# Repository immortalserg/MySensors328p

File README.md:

# MySensors328p

Проект по разработке оборудования на микросхеме Atmega328p+Nrf24l01+

## MySensorsKey

4-х клавишный сенсорный выключатель
- беспроводной приемник-передатчик nrf24l01+
- управляющий процессор Atmega 328p с возможностью шифрования (ATSHA204-TSU) и дополнительной памятью (AT25xx).
- 4 сенсорные кнопки на микросхеме TTP224
- встроенный датчик температуры, давления и влажности BME280
- встроенный USB-UART преобразователь на микросхеме CP2102
- контроллер заряда аккумулятора (TP4056)
- аккумулятор 3,7 В формафактора до 70мм-50мм (рекомендуемый 305570 (55мм-70мм-3мм))

Корпус https://www.tinkercad.com/things/eCkWAxR6Mgm-mysensorskey#/

## MysensorsSensor

Универсальный датчик
- беспроводной приемник-передатчик nrf24l01+
- управляющий процессор Atmega 328p с возможностью шифрования (ATSHA204-TSU) и дополнительной памятью (AT25xx).
- встроенный датчик температуры, давления и влажности BME280
- встроенный USB-UART преобразователь на микросхеме CP2102
- контроллер заряда аккумулятора (TP4056)
- счетчик DS2423
- дополнительные выводы Atmega 328p
- аккумулятор 3,7 В формафактора 402020(20мм-20мм-4мм), 502020(20мм-20мм-5мм), 602020(20мм-20мм-5мм)

## MySensorsShield

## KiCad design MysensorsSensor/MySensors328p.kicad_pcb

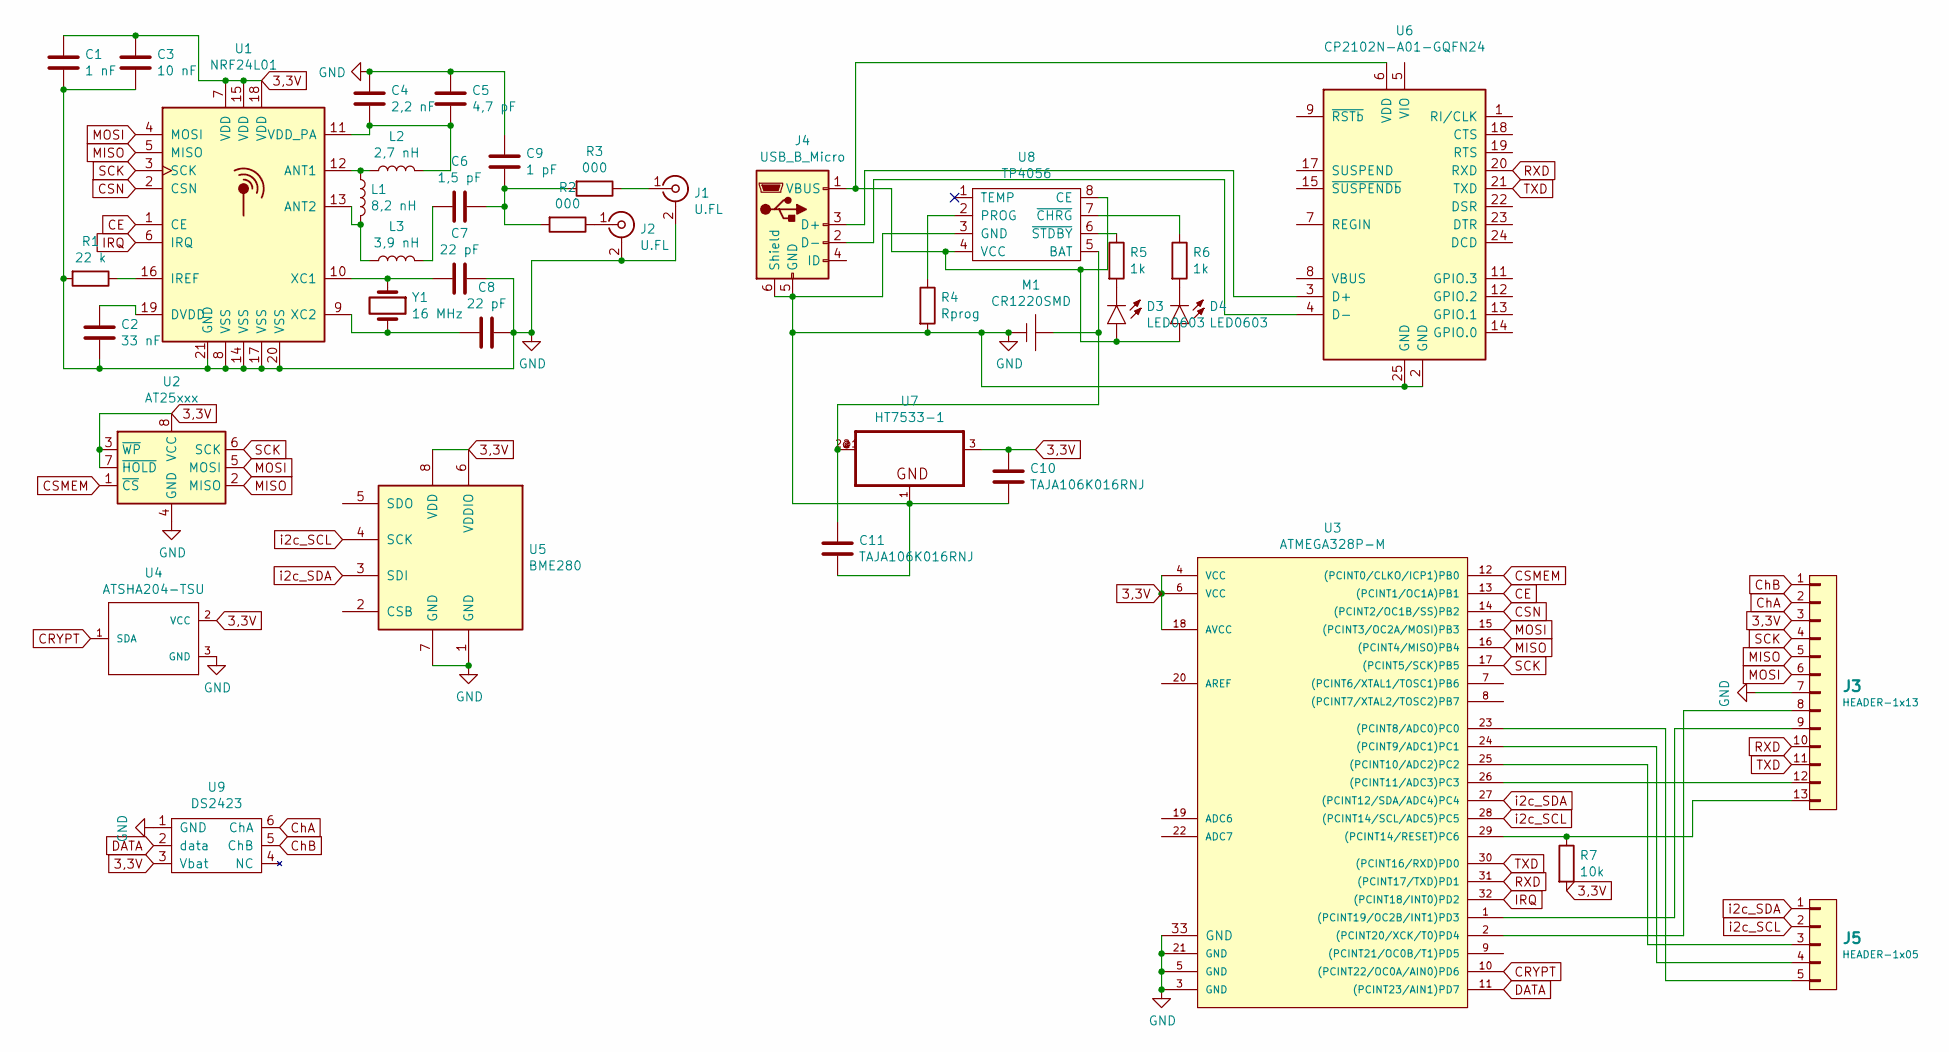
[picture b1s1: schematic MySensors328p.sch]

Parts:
C1: 1 nF; C_0402_1005Metric
C2: 33 nF; C_0402_1005Metric
C3: 10 nF; C_0402_1005Metric
C4: 2,2 nF; C_0402_1005Metric
C5: 4,7 pF; C_0402_1005Metric
C6: 1,5 pF; C_0402_1005Metric
C7, C8: 22 pF; C_0402_1005Metric
C9: 1 pF; C_0402_1005Metric
C10, C11: TAJA106K016RNJ; C_1206_3216Metric
D3, D4: LED0603; LED-0603
J1: U.FL; Texas_SWRA117D_2.4GHz_Right
J2: U.FL; U.FL_Hirose_U.FL-R-SMT-1_Vertical
J3: HEADER-1x13; PinHeader_1x13_P1.27mm_Vertical
J4: USB_B_Micro; USB_Micro-B_Molex_47346-0001
J5: HEADER-1x05; PinHeader_1x05_P1.27mm_Vertical
L1: 8,2 nH; L_0402_1005Metric
L2: 2,7 nH; L_0402_1005Metric
L3: 3,9 nH; L_0402_1005Metric
M1: CR1220SMD; WP-50mil-1x02
R1: 22 k; R_0402_1005Metric
R2, R3: 000; R_0402_1005Metric
R4: Rprog; R_0402_1005Metric
R5, R6: 1k; R_0402_1005Metric
R7: 10k; R_0402_1005Metric
U1: NRF24L01; QFN-20-1EP_4x4mm_P0.5mm_EP2.5x2.5mm
U2: AT25xxx; SOIC-8_3.9x4.9mm_P1.27mm
U3: ATMEGA328P-M; QFN-32-1EP_5x5mm_P0.5mm_EP3.45x3.45mm
U4: ATSHA204-TSU; SOT-23
U5: BME280; bme280
U6: CP2102N-A01-GQFN24; QFN-24-1EP_4x4mm_P0.5mm_EP2.6x2.6mm
U7: HT7533-1; SOT-89-3
U8: TP4056; PPSOP8
U9: DS2423; tsoc-6
Y1: 16 MHz; Crystal_SMD_5032-2Pin_5.0x3.2mm

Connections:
3,3V: C1.1, C3.1, C10.1, J3.3, R7.2, U1.7 (VDD), U1.15 (VDD), U1.18 (VDD), U2.3 (~WP), U2.7 (~HOLD), U2.8 (VCC), U3.4 (VCC), U3.6 (VCC), U3.18 (AVCC), U4.2 (VCC), U5.6 (VDDIO), U5.8 (VDD), U7.3 (VO), U9.3 (Vbat)
CE: U1.1 (CE), U3.13 ((PCINT1/OC1A)PB1)
CRYPT: U3.10 ((PCINT22/OC0A/AIN0)PD6), U4.1 (SDA)
CSMEM: U2.1 (~CS), U3.12 ((PCINT0/CLKO/ICP1)PB0)
CSN: U1.2 (CSN), U3.14 ((PCINT2/OC1B/SS)PB2)
ChA: J3.2, U9.6 (ChA)
ChB: J3.1, U9.5 (ChB)
DATA: U3.11 ((PCINT23/AIN1)PD7), U9.2 (data)
GND: C1.2, C2.2, C3.2, C4.1, C5.1, C7.1, C8.1, C9.1, C10.2, C11.2, J1.2 (Ext), J2.2 (Ext), J3.7, J4.5 (GND), J4.6 (Shield), M1.1 (-), R1.2, R4.2, U1.8 (VSS), U1.14 (VSS), U1.17 (VSS), U1.20 (VSS), U1.21 (GND), U2.4 (GND), U3.3 (GND), U3.5 (GND), U3.21 (GND), U3.33 (GND), U4.3 (GND), U5.1 (GND), U5.7 (GND), U6.2 (GND), U6.25 (GND), U7.1 (GND), U8.3 (GND), U9.1 (GND)
IRQ: U1.6 (IRQ), U3.32 ((PCINT18/INT0)PD2)
MISO: J3.5, U1.5 (MISO), U2.2 (MISO), U3.16 ((PCINT4/MISO)PB4)
MOSI: J3.6, U1.4 (MOSI), U2.5 (MOSI), U3.15 ((PCINT3/OC2A/MOSI)PB3)
unnamed: C2.1, U1.19 (DVDD)
unnamed: C4.2, C5.2, L2.2, U1.11 (VDD_PA)
unnamed: C6.1, C9.2, R2.2, R3.2
unnamed: C6.2, L3.2
unnamed: C7.2, U1.10 (XC1), Y1.1
unnamed: C8.2, U1.9 (XC2), Y1.2
unnamed: C11.1, M1.2 (+), U7.2 (VI), U7.2@1 (VI), U8.5 (BAT)
unnamed: D3.A, D4.A, J4.1 (VBUS), U6.6 (VDD), U8.4 (VCC), U8.8 (CE)
unnamed: D3.C, R5.2
unnamed: D4.C, R6.2
unnamed: J1.1 (In), R3.1
unnamed: J2.1 (In), R2.1
unnamed: J3.8, U3.2 ((PCINT20/XCK/T0)PD4)
unnamed: J3.9, U3.1 ((PCINT19/OC2B/INT1)PD3)
unnamed: J3.12, U3.26 ((PCINT11/ADC3)PC3)
unnamed: J3.13, R7.1, U3.29 ((PCINT14/RESET)PC6)
unnamed: J4.2 (D-), U6.4 (D-)
unnamed: J4.3 (D+), U6.3 (D+)
unnamed: J5.3, U3.25 ((PCINT10/ADC2)PC2)
unnamed: J5.4, U3.24 ((PCINT9/ADC1)PC1)
unnamed: J5.5, U3.23 ((PCINT8/ADC0)PC0)
unnamed: L1.1, L2.1, U1.12 (ANT1)
unnamed: L1.2, L3.1, U1.13 (ANT2)
unnamed: R1.1, U1.16 (IREF)
unnamed: R4.1, U8.2 (PROG)
unnamed: R5.1, U8.6 (~STDBY)
unnamed: R6.1, U8.7 (~CHRG)
RXD: J3.10, U3.31 ((PCINT17/TXD)PD1), U6.20 (RXD)
SCK: J3.4, U1.3 (SCK), U2.6 (SCK), U3.17 ((PCINT5/SCK)PB5)
TXD: J3.11, U3.30 ((PCINT16/RXD)PD0), U6.21 (TXD)
i2c_SCL: J5.2, U3.28 ((PCINT14/SCL/ADC5)PC5), U5.4 (SCK)
i2c_SDA: J5.1, U3.27 ((PCINT12/SDA/ADC4)PC4), U5.3 (SDI)

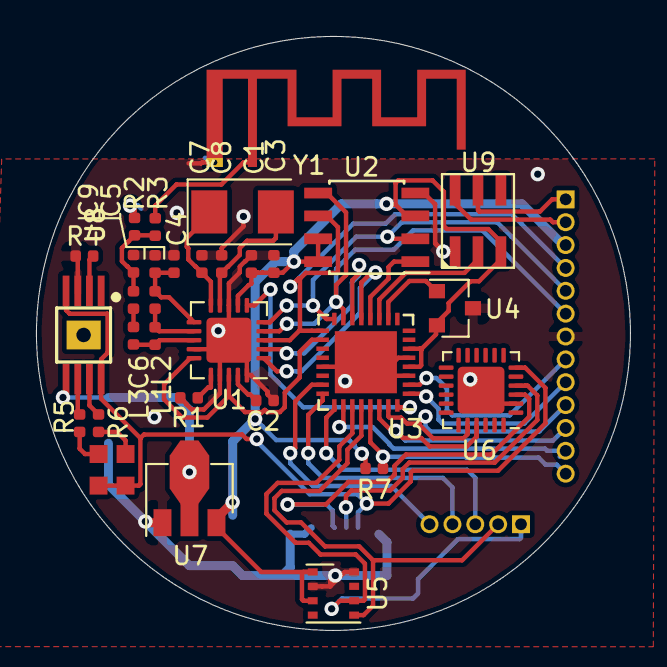
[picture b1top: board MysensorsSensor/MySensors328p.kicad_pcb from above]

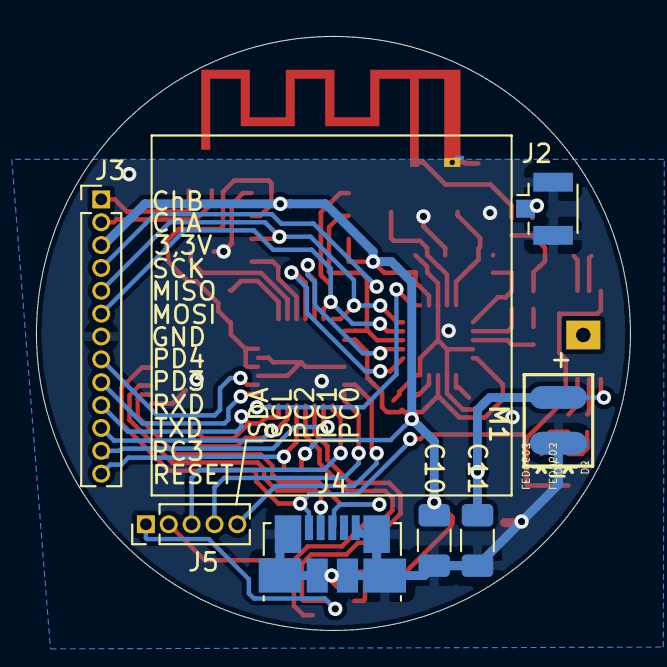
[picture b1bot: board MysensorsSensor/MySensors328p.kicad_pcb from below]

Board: 2 copper layers, 33.0 x 33.0 mm, 39 parts (7 on the bottom side), 44 nets.

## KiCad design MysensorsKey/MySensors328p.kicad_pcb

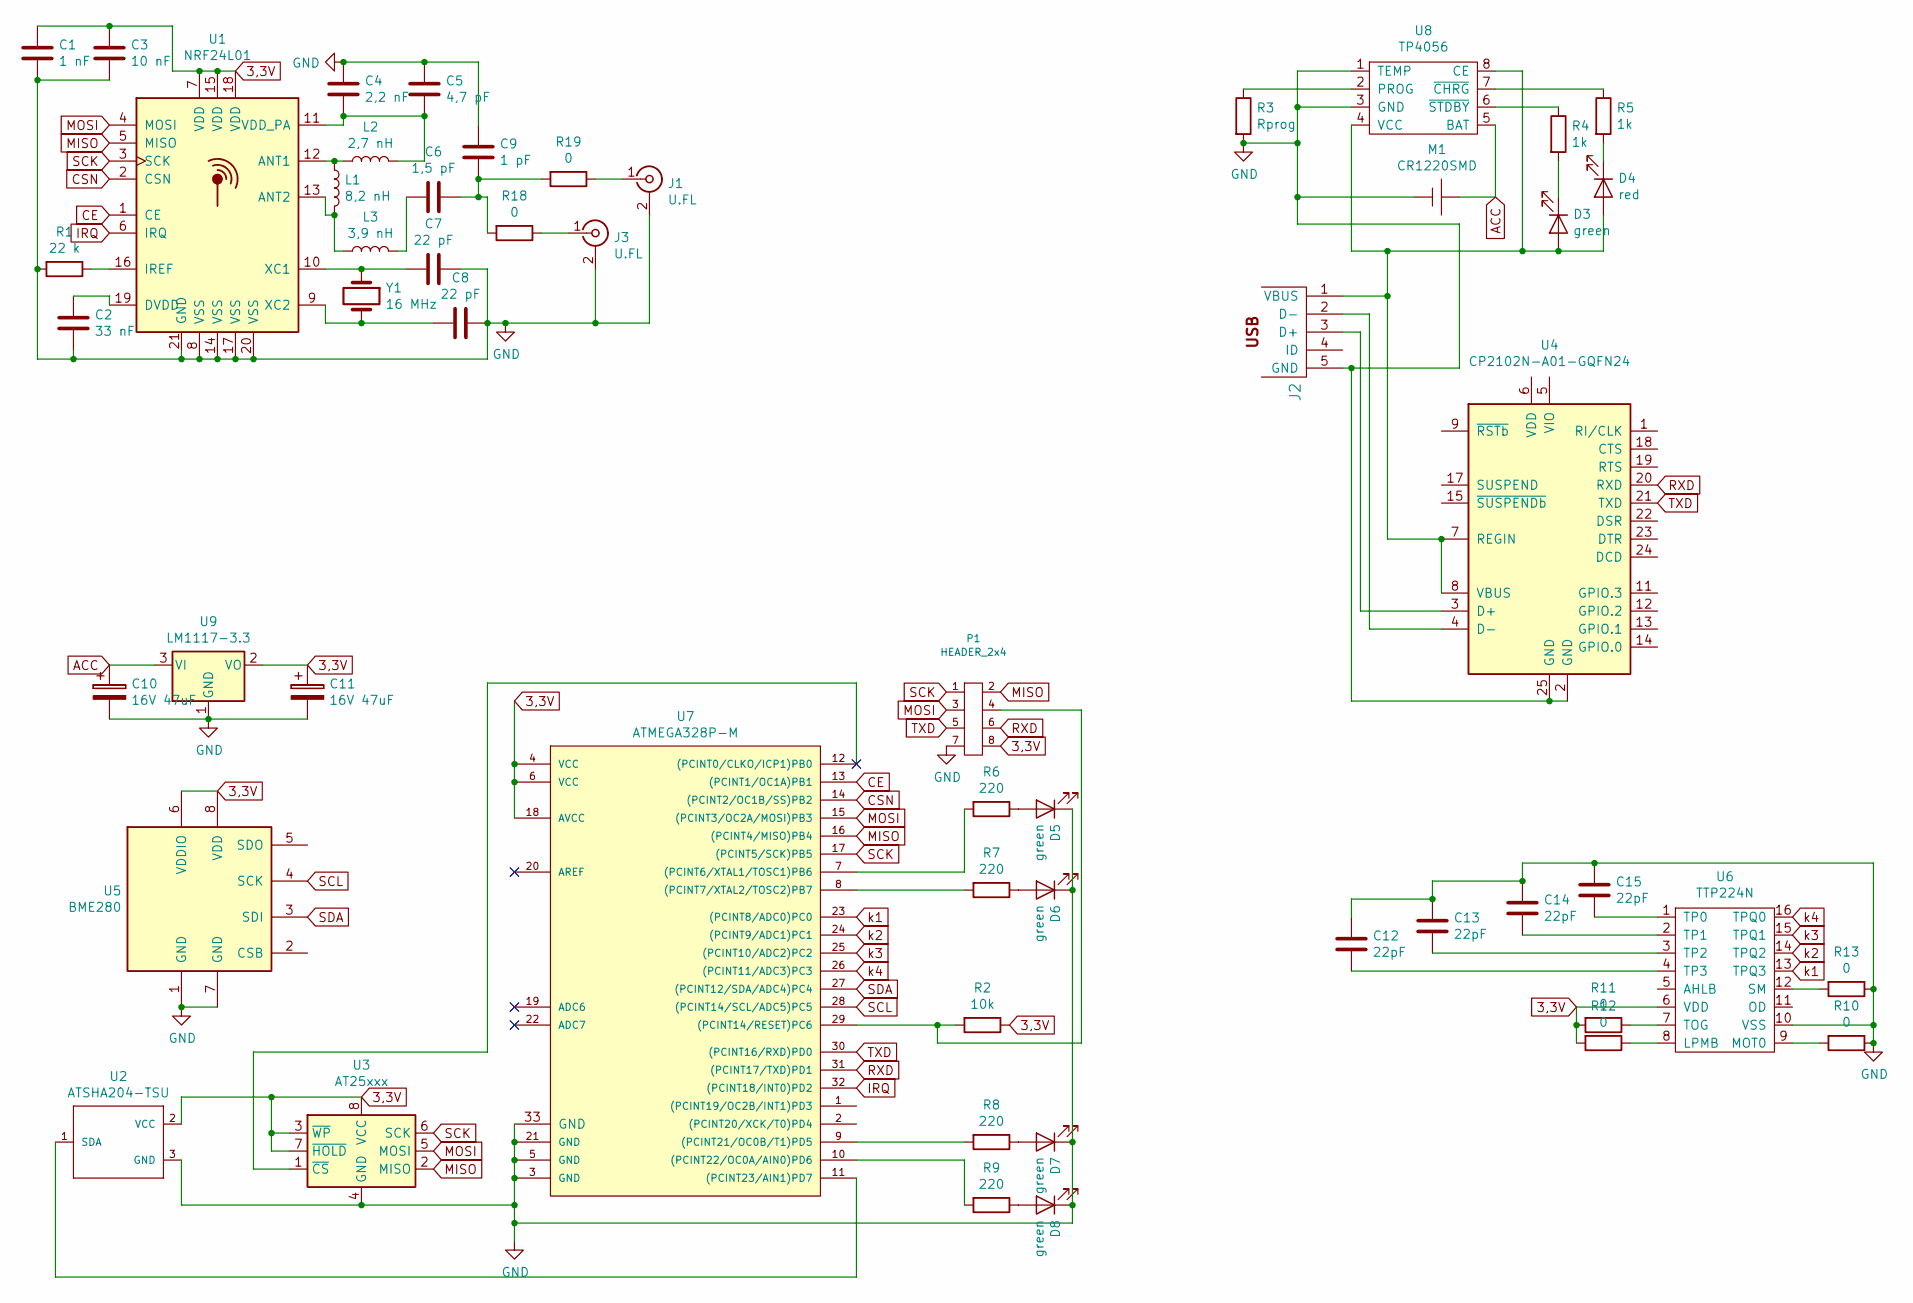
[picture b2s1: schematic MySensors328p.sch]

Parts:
C1: 1 nF; C_0402_1005Metric
C2: 33 nF; C_0402_1005Metric
C3: 10 nF; C_0402_1005Metric
C4: 2,2 nF; C_0402_1005Metric
C5: 4,7 pF; C_0402_1005Metric
C6: 1,5 pF; C_0402_1005Metric
C7, C8: 22 pF; C_0402_1005Metric
C9: 1 pF; C_0402_1005Metric
C10, C11: 16V 47uF; C_2816_7142Metric_Pad3.20x4.45mm_HandSolder
C12, C13, C14, C15: 22pF; C_0402_1005Metric
D3: green; D_0805_2012Metric_Pad1.15x1.40mm_HandSolder
D4: red; D_0805_2012Metric_Pad1.15x1.40mm_HandSolder
D5, D6, D7, D8: green; smd_led_4008
J1: U.FL; Texas_SWRA117D_2.4GHz_Right
J2: USBMINI; conn_usb_B_micro_smd-3
J3: U.FL; U.FL_Hirose_U.FL-R-SMT-1_Vertical
L1: 8,2 nH; L_0402_1005Metric
L2: 2,7 nH; L_0402_1005Metric
L3: 3,9 nH; L_0402_1005Metric
M1: CR1220SMD; WP-50mil-1x02
P1: HEADER_2x4; PinHeader_1x08_P1.27mm_Horizontal
R1: 22 k; R_0402_1005Metric
R2: 10k; R_0402_1005Metric
R3: Rprog; R_0402_1005Metric
R4, R5: 1k; R_0402_1005Metric
R6, R7, R8, R9: 220; R_0402_1005Metric
R10, R11, R12, R13, R18, R19: 0; R_0402_1005Metric
U1: NRF24L01; QFN-20-1EP_4x4mm_P0.5mm_EP2.5x2.5mm
U2: ATSHA204-TSU; SOT-23
U3: AT25xxx; SOIC-8_3.9x4.9mm_P1.27mm
U4: CP2102N-A01-GQFN24; QFN-24-1EP_4x4mm_P0.5mm_EP2.6x2.6mm
U5: BME280; bme280
U6: TTP224N; SSOP-16_3.9x4.9mm_P0.635mm
U7: ATMEGA328P-M; QFN-32-1EP_5x5mm_P0.5mm_EP3.45x3.45mm
U8: TP4056; SSOP-8_3.95x5.21x3.27mm_P1.27mm
U9: LM1117-3.3; SOT-223-3_TabPin2
Y1: 16 MHz; Crystal_SMD_MicroCrystal_CC7V-T1A-2Pin_3.2x1.5mm_HandSolder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

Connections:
3,3V: C1.1, C3.1, C11.1, P1.8, R2.1, R11.2, R12.2, U1.7 (VDD), U1.15 (VDD), U1.18 (VDD), U2.2 (VCC), U3.3 (~WP), U3.7 (~HOLD), U3.8 (VCC), U5.6 (VDDIO), U5.8 (VDD), U6.6 (VDD), U7.4 (VCC), U7.6 (VCC), U7.18 (AVCC), U9.2 (VO)
ACC: C10.1, M1.2 (+), U8.5 (BAT), U9.3 (VI)
CE: U1.1 (CE), U7.13 ((PCINT1/OC1A)PB1)
CSN: U1.2 (CSN), U7.14 ((PCINT2/OC1B/SS)PB2)
GND: C1.2, C2.2, C3.2, C4.1, C5.1, C7.1, C8.1, C9.1, C10.2, C11.2, C12.1, C13.1, C14.1, C15.1, D5.1 (K), D6.1 (K), D7.1 (K), D8.1 (K), J1.2 (Ext), J2.5 (GND), J3.2 (Ext), M1.1 (-), P1.7, R1.2, R3.2, R10.1, R13.1, U1.8 (VSS), U1.14 (VSS), U1.17 (VSS), U1.20 (VSS), U1.21 (GND), U2.3 (GND), U3.4 (GND), U4.2 (GND), U4.25 (GND), U5.1 (GND), U5.7 (GND), U6.10 (VSS), U7.3 (GND), U7.5 (GND), U7.21 (GND), U7.33 (GND), U8.1 (TEMP), U8.3 (GND), U9.1 (GND)
IRQ: U1.6 (IRQ), U7.32 ((PCINT18/INT0)PD2)
MISO: P1.2 (P1), U1.5 (MISO), U3.2 (MISO), U7.16 ((PCINT4/MISO)PB4)
MOSI: P1.3 (P2), U1.4 (MOSI), U3.5 (MOSI), U7.15 ((PCINT3/OC2A/MOSI)PB3)
unnamed: C2.1, U1.19 (DVDD)
unnamed: C4.2, C5.2, L2.2, U1.11 (VDD_PA)
unnamed: C6.1, C9.2, R18.2, R19.2
unnamed: C6.2, L3.2
unnamed: C7.2, U1.10 (XC1), Y1.1
unnamed: C8.2, U1.9 (XC2), Y1.2
unnamed: C12.2, U6.4 (TP3)
unnamed: C13.2, U6.3 (TP2)
unnamed: C14.2, U6.2 (TP1)
unnamed: C15.2, U6.1 (TP0)
unnamed: D3.1 (K), R4.2
unnamed: D3.2 (A), D4.2 (A), J2.1 (VBUS), U4.7 (REGIN), U4.8 (VBUS), U8.4 (VCC), U8.8 (CE)
unnamed: D4.1 (K), R5.2
unnamed: D5.2 (A), R6.1
unnamed: D6.2 (A), R7.1
unnamed: D7.2 (A), R8.1
unnamed: D8.2 (A), R9.1
unnamed: J1.1 (In), R19.1
unnamed: J2.2 (D-), U4.4 (D-)
unnamed: J2.3 (D+), U4.3 (D+)
unnamed: J3.1 (In), R18.1
unnamed: L1.1, L2.1, U1.12 (ANT1)
unnamed: L1.2, L3.1, U1.13 (ANT2)
unnamed: P1.4 (P2), R2.2, U7.29 ((PCINT14/RESET)PC6)
unnamed: R1.1, U1.16 (IREF)
unnamed: R3.1, U8.2 (PROG)
unnamed: R4.1, U8.6 (~STDBY)
unnamed: R5.1, U8.7 (~CHRG)
unnamed: R6.2, U7.7 ((PCINT6/XTAL1/TOSC1)PB6)
unnamed: R7.2, U7.8 ((PCINT7/XTAL2/TOSC2)PB7)
unnamed: R8.2, U7.9 ((PCINT21/OC0B/T1)PD5)
unnamed: R9.2, U7.10 ((PCINT22/OC0A/AIN0)PD6)
unnamed: R10.2, U6.9 (MOT0)
unnamed: R11.1, U6.7 (TOG)
unnamed: R12.1, U6.8 (LPMB)
unnamed: R13.2, U6.12 (SM)
unnamed: U2.1 (SDA), U7.11 ((PCINT23/AIN1)PD7)
unnamed: U3.1 (~CS), U7.12 ((PCINT0/CLKO/ICP1)PB0)
RXD: P1.6, U4.20 (RXD), U7.31 ((PCINT17/TXD)PD1)
SCK: P1.1, U1.3 (SCK), U3.6 (SCK), U7.17 ((PCINT5/SCK)PB5)
SCL: U5.4 (SCK), U7.28 ((PCINT14/SCL/ADC5)PC5)
SDA: U5.3 (SDI), U7.27 ((PCINT12/SDA/ADC4)PC4)
TXD: P1.5, U4.21 (TXD), U7.30 ((PCINT16/RXD)PD0)
k1: U6.13 (TPQ3), U7.23 ((PCINT8/ADC0)PC0)
k2: U6.14 (TPQ2), U7.24 ((PCINT9/ADC1)PC1)
k3: U6.15 (TPQ1), U7.25 ((PCINT10/ADC2)PC2)
k4: U6.16 (TPQ0), U7.26 ((PCINT11/ADC3)PC3)

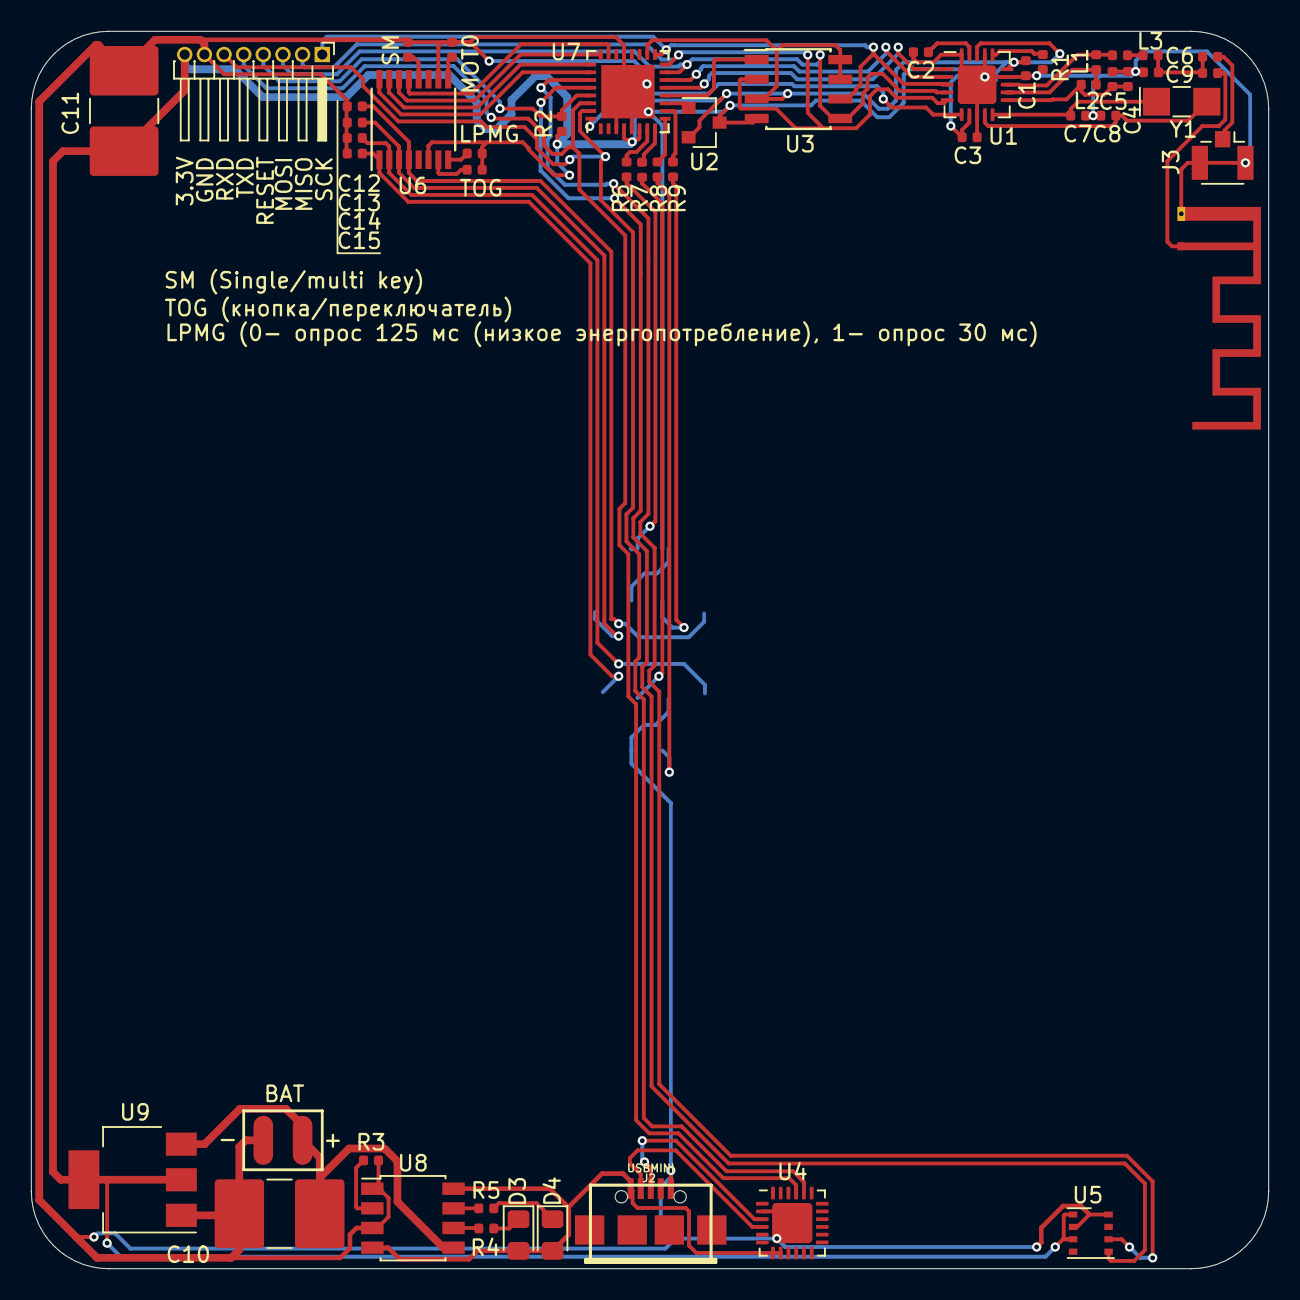
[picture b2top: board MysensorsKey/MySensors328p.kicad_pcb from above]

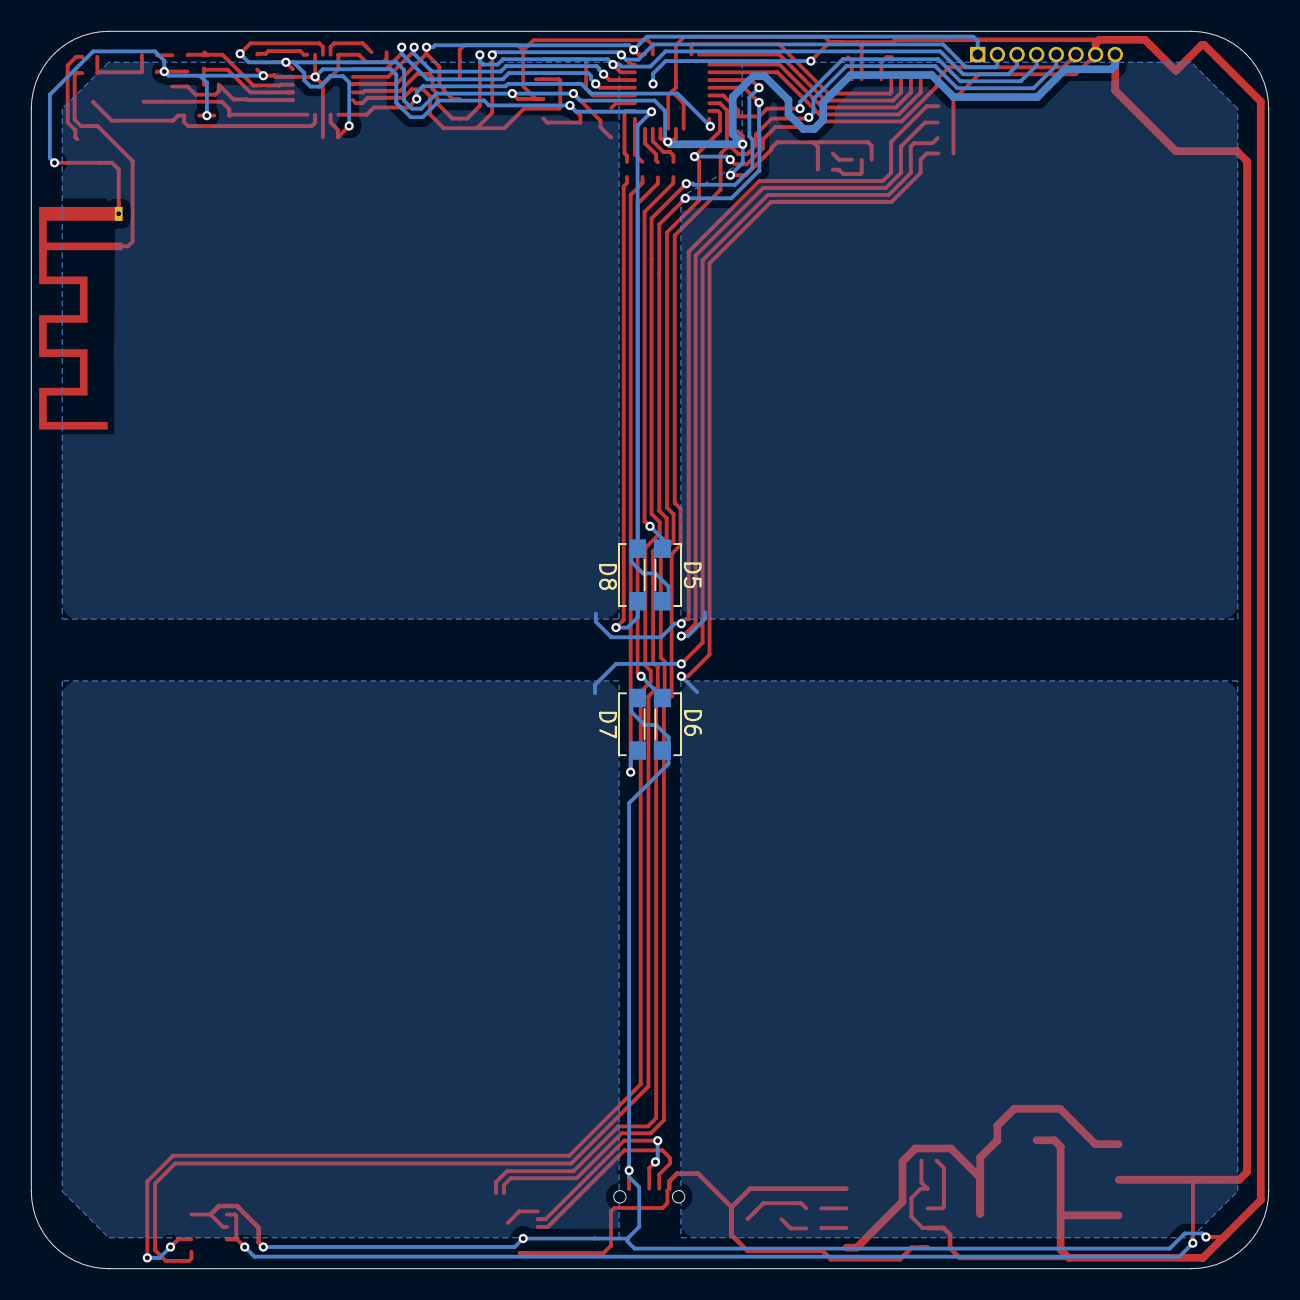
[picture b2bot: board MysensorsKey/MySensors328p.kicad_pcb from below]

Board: 2 copper layers, 80.0 x 80.0 mm, 54 parts (4 on the bottom side), 55 nets.

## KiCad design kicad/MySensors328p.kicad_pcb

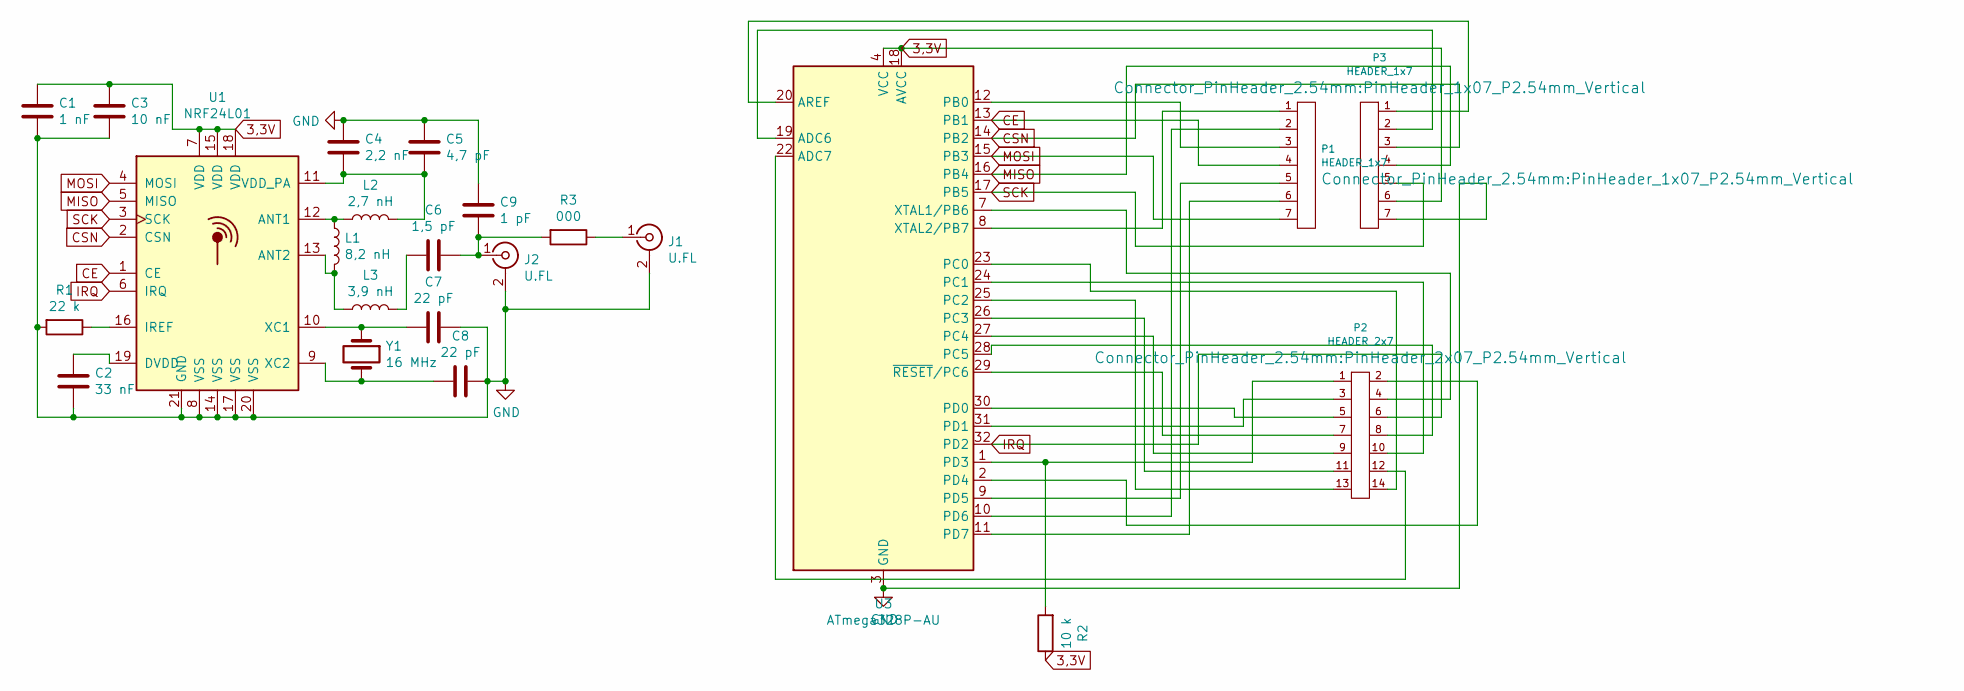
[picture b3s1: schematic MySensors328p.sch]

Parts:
C1: 1 nF; C_0402_1005Metric
C2: 33 nF; C_0402_1005Metric
C3: 10 nF; C_0402_1005Metric
C4: 2,2 nF; C_0402_1005Metric
C5: 4,7 pF; C_0402_1005Metric
C6: 1,5 pF; C_0402_1005Metric
C7, C8: 22 pF; C_0402_1005Metric
C9: 1 pF; C_0402_1005Metric
J1: U.FL; Texas_SWRA117D_2.4GHz_Left
J2: U.FL; coaxial_u.fl-r-smt-1
L1: 8,2 nH; L_0402_1005Metric
L2: 2,7 nH; L_0402_1005Metric
L3: 3,9 nH; L_0402_1005Metric
P1, P3: HEADER_1x7; PinHeader_1x07_P2.54mm_Vertical
P2: HEADER_2x7; PinHeader_2x07_P2.54mm_Vertical
R1: 22 k; R_0402_1005Metric
R2: 10 k; R_0402_1005Metric
R3: 000; R_0402_1005Metric
U1: NRF24L01; QFN-20-1EP_4x4mm_P0.5mm_EP2.5x2.5mm
U3: ATmega328P-AU; TQFP-32_7x7mm_P0.8mm
Y1: 16 MHz; Crystal_SMD_5032-2Pin_5.0x3.2mm

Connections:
3,3V: C1.1, C3.1, P3.6, R2.1, U1.7 (VDD), U1.15 (VDD), U1.18 (VDD), U3.4 (VCC), U3.6 (VCC), U3.18 (AVCC)
CE: P1.4, U1.1 (CE), U3.13 (PB1)
CSN: P3.3, U1.2 (CSN), U3.14 (PB2)
GND: C1.2, C2.2, C3.2, C4.1, C5.1, C7.1, C8.1, C9.1, J1.2 (Ext), J2.2 (Ext), P3.7, R1.2, U1.8 (VSS), U1.14 (VSS), U1.17 (VSS), U1.20 (VSS), U1.21 (GND), U3.3 (GND), U3.5 (GND), U3.21 (GND)
IRQ: P2.6 (P3), U1.6 (IRQ), U3.32 (PD2)
MISO: P3.4, U1.5 (MISO), U3.16 (PB4)
MOSI: P1.7, U1.4 (MOSI), U3.15 (PB3)
unnamed: C2.1, U1.19 (DVDD)
unnamed: C4.2, C5.2, L2.2, U1.11 (VDD_PA)
unnamed: C6.1, C9.2, J2.1 (In), R3.2
unnamed: C6.2, L3.2
unnamed: C7.2, U1.10 (XC1), Y1.1
unnamed: C8.2, U1.9 (XC2), Y1.2
unnamed: J1.1 (In), R3.1
unnamed: L1.1, L2.1, U1.12 (ANT1)
unnamed: L1.2, L3.1, U1.13 (ANT2)
unnamed: P1.1, U3.8 (XTAL2/PB7)
unnamed: P1.2, U3.10 (PD6)
unnamed: P1.3, U3.12 (PB0)
unnamed: P1.5, U3.9 (PD5)
unnamed: P1.6, U3.11 (PD7)
unnamed: P2.1, R2.2, U3.1 (PD3)
unnamed: P2.2 (P1), U3.2 (PD4)
unnamed: P2.3 (P2), U3.31 (PD1)
unnamed: P2.4 (P2), U3.7 (XTAL1/PB6)
unnamed: P2.5 (P3), U3.30 (PD0)
unnamed: P2.7 (P4), U3.29 (~RESET~/PC6)
unnamed: P2.8 (P4), U3.28 (PC5)
unnamed: P2.9 (P5), U3.27 (PC4)
unnamed: P2.10 (P5), U3.24 (PC1)
unnamed: P2.11 (P6), U3.26 (PC3)
unnamed: P2.12 (P6), U3.22 (ADC7)
unnamed: P2.13 (P7), U3.25 (PC2)
unnamed: P2.14 (P7), U3.23 (PC0)
unnamed: P3.1, U3.20 (AREF)
unnamed: P3.2, U3.19 (ADC6)
unnamed: R1.1, U1.16 (IREF)
SCK: P3.5, U1.3 (SCK), U3.17 (PB5)

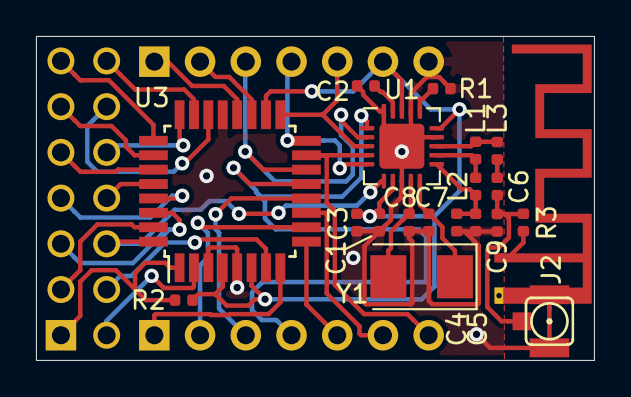
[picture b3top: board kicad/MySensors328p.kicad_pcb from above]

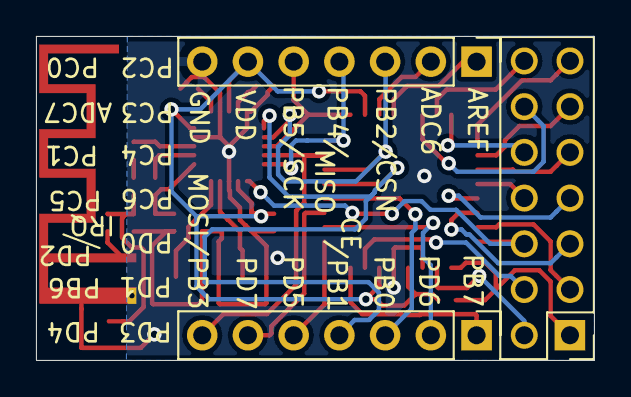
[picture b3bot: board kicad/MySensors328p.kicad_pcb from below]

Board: 2 copper layers, 31.0 x 18.0 mm, 23 parts (3 on the bottom side), 38 nets.
